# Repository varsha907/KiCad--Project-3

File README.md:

# KiCad--Project-3
My first microcontroller break-out board project
# ESP-12 Wi-Fi Development Board PCB Design

## Project Overview
This project is a custom PCB design based on the ESP-12 (ESP8266) Wi-Fi module, created using KiCad. The board is designed to provide a compact and reliable platform for IoT and embedded system applications.

## Features
- ESP-12 (ESP8266) Wi-Fi Module
- USB-to-Serial Programming Interface
- 3.3V Power Supply Circuit
- Reset and Flash Buttons
- GPIO Header Connections
- Compact PCB Layout
- Designed in KiCad

## Software Used
- KiCad 9

## Project Files
- `.kicad_pro` - KiCad project file
- `.kicad_sch` - Schematic design
- `.kicad_pcb` - PCB layout
- `Gerber Files` - Manufacturing files
- `Drill Files` - PCB drilling information
- `Libraries` - Custom symbols and footprints 

## Design Flow
1. Circuit schematic creation.
2. Component selection and footprint assignment.
3. PCB layout design.
4. Design Rule Check (DRC).
5. Gerber generation for manufacturing.

## Applications
- Internet of Things (IoT)
- Home Automation
- Wireless Sensor Networks
- Embedded Systems
- Wi-Fi Enabled Projects

## PCB Preview
Add screenshots of the schematic and PCB layout here.

### Schematic

### PCB Layout

## Author
Varsha Kumari

## License
This project is shared for educational and portfolio purposes.

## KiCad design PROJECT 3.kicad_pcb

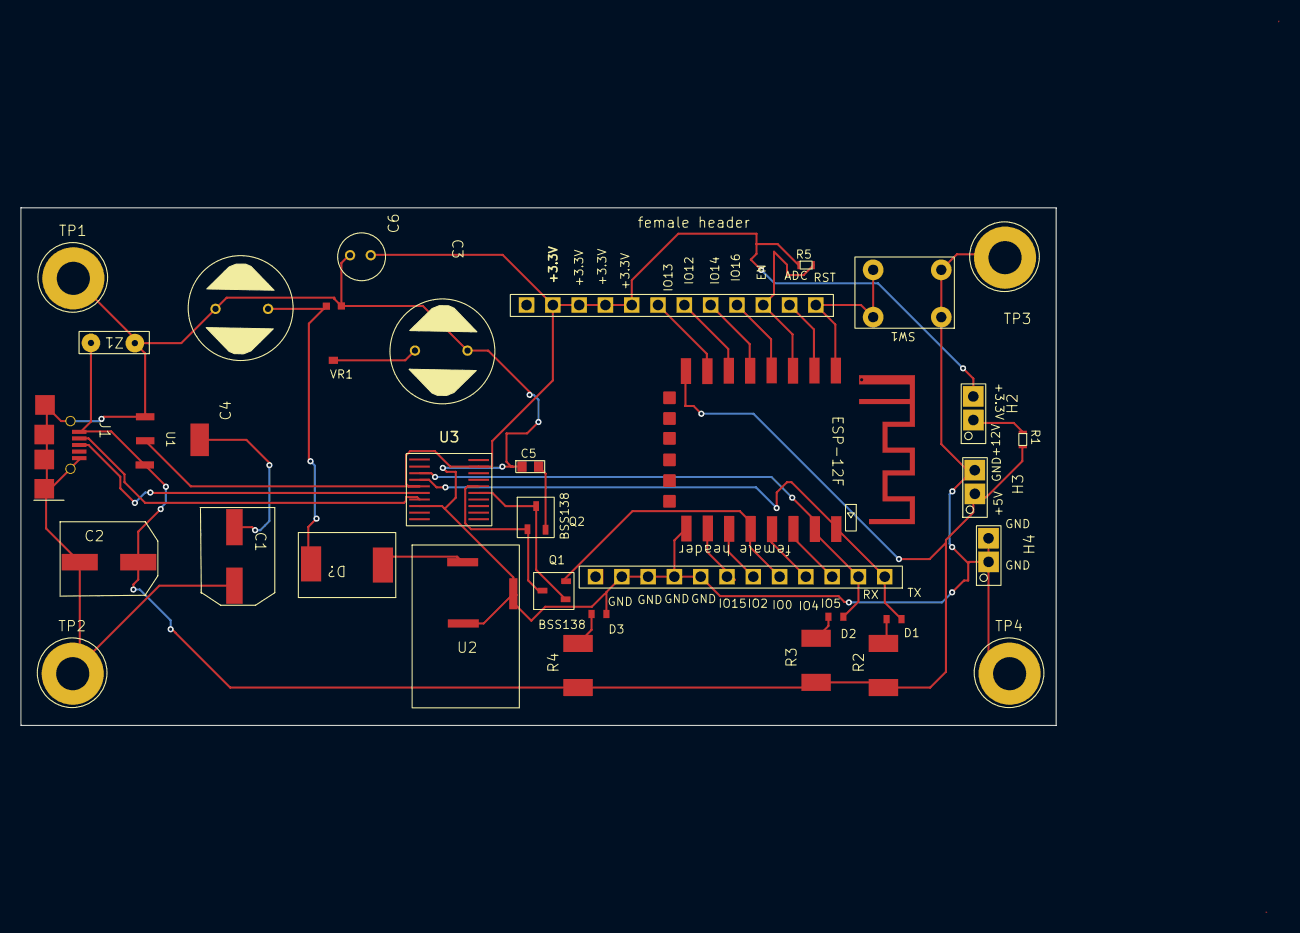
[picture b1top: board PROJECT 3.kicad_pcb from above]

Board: 2 copper layers, 100.0 x 50.0 mm, 34 parts (0 on the bottom side), 30 nets.

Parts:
C1, C2: 10uF; 865080343009(10uf SMD capacitor)
C3, C4: 1000uF; 1mF capacitor
C5: 1uF; MOLDED CAPACITORS, T50 _ T51 _ T55 _ T56 _ 04051 TYPES (DIM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
C6: 100nF
D1, D2, D3: Standard 0603 SMD LED
D4: SS32 - S310(Schottky diode)
H1, H5: 12 pin femaile onnector
H2, H3, H4: 2pin female header
J1: USB MICRO TYPE B(SMT)
M1: ESP-12
Q1, Q2: BSS138(SOT−23 (TO−236) 2.90x1.30x1.00 1.90P)
R1, R5: 10K; 10k SMD RESISTER(RC0603)(1.6_0.8mm)
R2, R3, R4: 1K; SMD RESISTER(RCV2010 e3)
SW1: PTS645 Tactile Switches(6mm)
TP1: 3.2mm; mounting holes(3.2mm)
TP2, TP3, TP4: mounting holes(3.2mm)
U1: AMS1117
U2: 12V DC JACK
U3: CH340T
VR1: 12v; Trimmer Potentiometer( SMD Open Type 2mm Size PVZ2A Series)
Z1: 5V5; zener diode(5v)

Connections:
+3.3V: C6.2, H1.8, H1.9, H1.10, H1.11, H2.2, R5.1, U1.2, U3.5 (V3), U3.19 (VCC)
+5V: C2.1, H3.1, J1.1 (VBUS), M1.8 (VCC), R1.2, R2.1, R3.1, R4.1, U1.3, Z1.2
+12V: H2.1, R1.1
/ADC: H1.2, M1.2 (ADC)
/D+: J1.3 (D+), U3.6 (UD+/D+)
/D-: J1.2 (D-), U3.7 (UD-/D-)
/DTR: Q1.2, Q2.1, U3.15 (DTR)
/EN: H1.3, M1.3 (EN), R5.2
/IO0: H5.5, M1.12 (GPIO0), Q1.3
/IO2: H5.6, M1.11 (GPIO2)
/IO4: H5.4, M1.13 (GPIO4)
/IO5: H5.3, M1.14 (GPIO5)
/IO12: H1.6, M1.6 (GPIO12)
/IO13: H1.7, M1.7 (GPIO13)
/IO14: H1.5, M1.5 (GPIO14)
/IO15: H5.7, M1.10 (GPIO15)
/IO16: H1.4, M1.4 (GPIO)
/RST: H1.1, M1.1 (RST), SW1.3, SW1.4
/RX: D2.2, H5.2, M1.15 (RXD0), U3.3 (TXD)
/TX: D1.2, H5.1, M1.16 (TXD0), U3.4 (RXD)
GND: C1.1, C2.2, C3.1, C4.1, C5.2, C6.1, D3.2, H3.2, H4.1, H4.2, H5.8, H5.9, H5.10, H5.11, J1.5 (GND), J1.6 (MNT1), J1.7 (MNT2), J1.8 (MNT3), J1.9 (MNT4), J1.10 (MNT5), J1.11 (MNT6), M1.9 (GND), SW1.1, SW1.2, TP1.1, TP2.1, TP3.1, TP4.1, U1.1, U2.2, U2.3, U3.8 (GND), VR1.1, Z1.1
unnamed: C1.2, U1.4
unnamed: C3.2, VR1.3
unnamed: C4.2, D4.2, VR1.2
unnamed: C5.1, Q2.3
unnamed: D1.1, R2.2
unnamed: D2.1, R3.2
unnamed: D3.1, R4.2
unnamed: D4.1, U2.1
unnamed: Q1.1, Q2.2, U3.16 (RTS#)

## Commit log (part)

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2026-06-28 Expand README with project details and applications
    Added detailed project overview, features, software used, design flow, applications, and author information.
2026-06-28 Revise Libraries section description in README
    Clarified the description of the Libraries section in README.
2026-06-28 Fix image paths in README.md
    Updated image paths for schematic and PCB layout in README.
2026-06-28 Add MIT License to the project
